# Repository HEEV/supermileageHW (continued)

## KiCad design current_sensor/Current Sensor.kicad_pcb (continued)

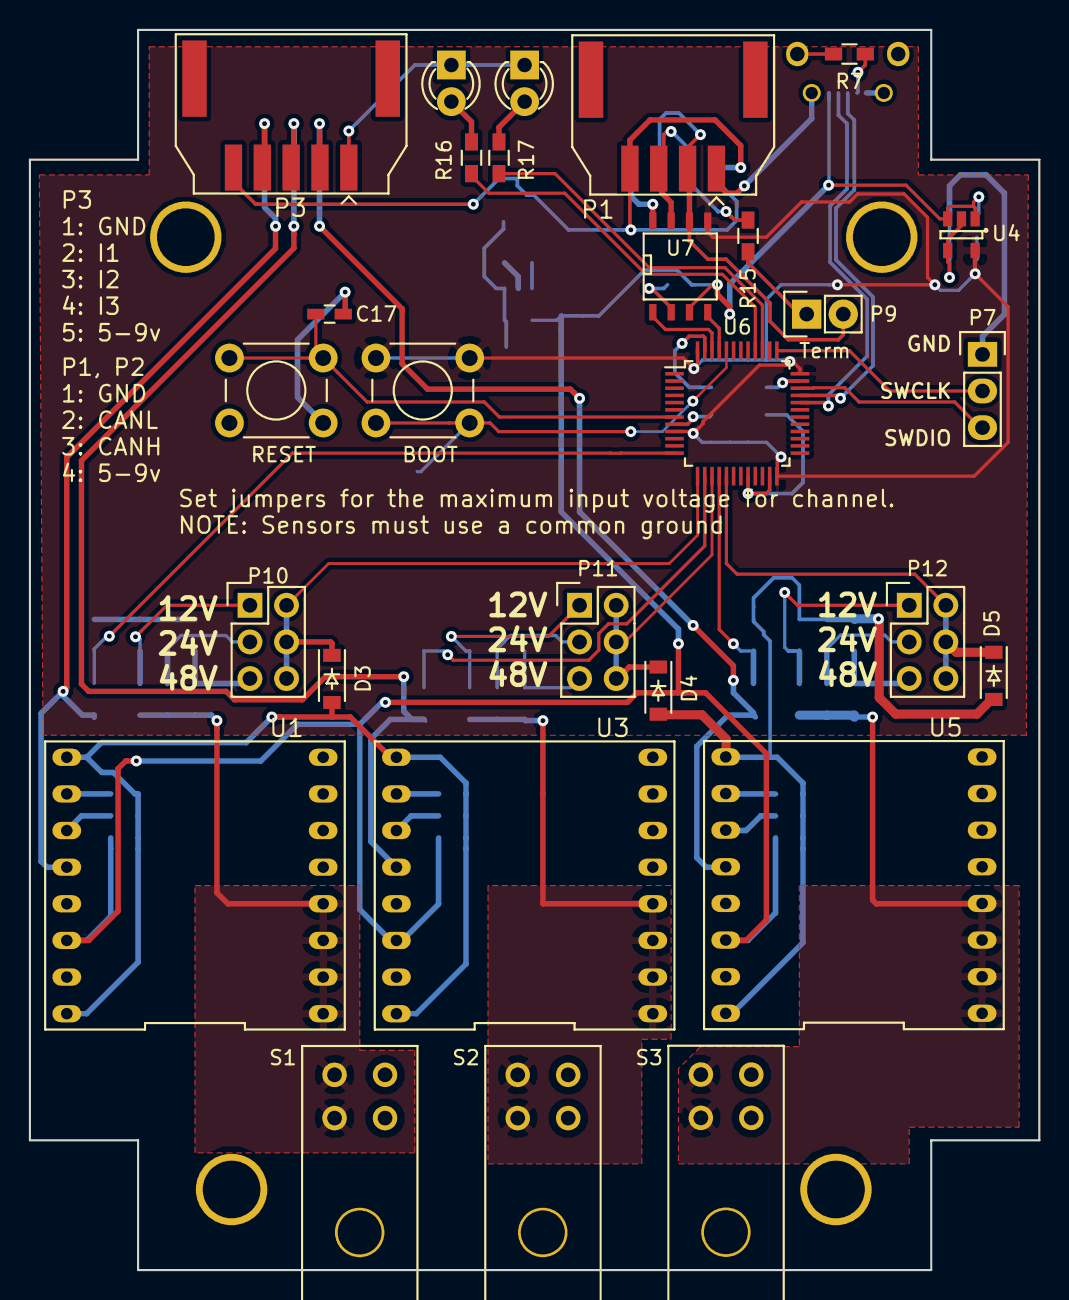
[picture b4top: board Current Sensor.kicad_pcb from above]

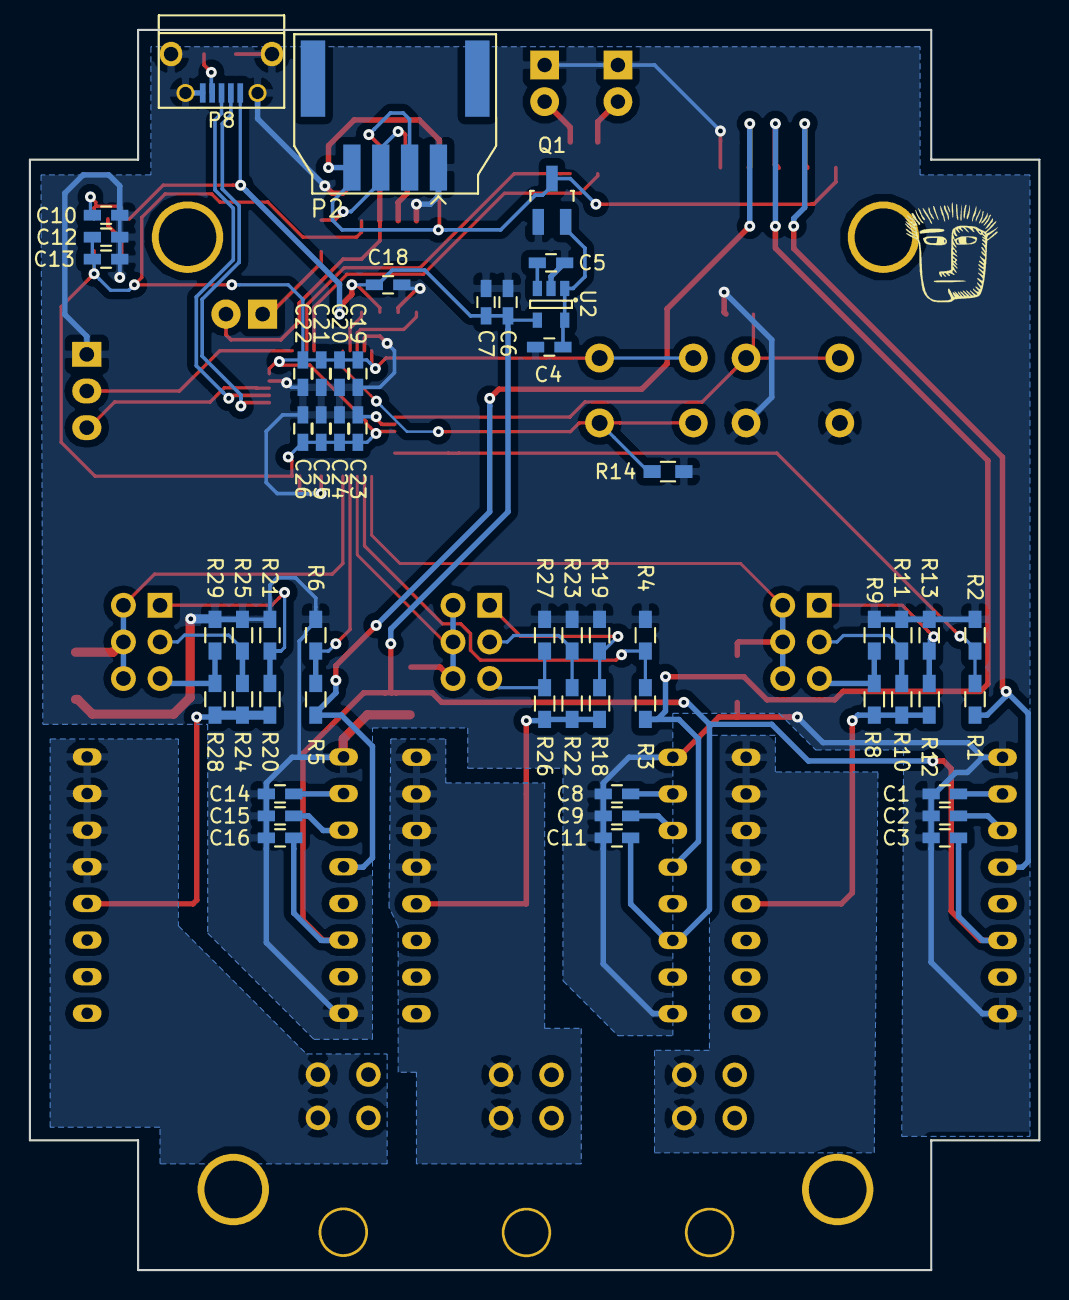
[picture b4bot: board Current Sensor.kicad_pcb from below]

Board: 2 copper layers, 70.0 x 86.0 mm, 82 parts (54 on the bottom side), 52 nets.

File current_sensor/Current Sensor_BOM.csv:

Reference,Value,Footprint,Count,Datasheet,FootprintLib,Distributor,PN
C1;C8;C14,1nf,C_0603_HandSoldering,3,,Capacitors_SMD,,
C23;C25;C21;C19,1uf,C_0603_HandSoldering,4,,Capacitors_SMD,Mouser,80-C0603C105K8P
C4;C5;C6;C3;C11;C16;C10;C13;C24;C18;C17;C26;C22;C20,0.1uf,C_0603_HandSoldering,14,,Capacitors_SMD,,
C7;C12,10uf,C_0603_HandSoldering,2,,Capacitors_SMD,,
C9;C15;C2,4.7nf,C_0603_HandSoldering,3,,Capacitors_SMD,,
D1,LED1,LED-3MM,1,,LEDs,,
D2,LED2,LED-3MM,1,,LEDs,,
D4;D3;D5;D7;D6;D8,D_Schottky_Small,SOD-123,6,,Diodes_SMD,Mouser,512-SS14FL 
P1,CAN_IN,Molex-duraClick-4conn,1,,User_Connectors,Mouser,538-502352-0400 
P10;P11;P12,CONN_02X03,Pin_Header_Straight_2x03,3,,Pin_Headers,,
P2,CAN_OUT,Molex-duraClick-4conn,1,,User_Connectors,Mouser,538-502352-0400 
P3,DuraClik-5,Molex-duraClick-5conn,1,,User_Connectors,Mouser,538-502352-0501 
P4;P5;P6,Ultra-Fit,Molex-UltraFit-2p,3,,Supermileage,Mouser,538-172310-2102 
P7,CONN_01X03,Pin_Header_Straight_1x03,1,,Pin_Headers,,
P8,USB,USB_Micro-B,1,,Connect,Mouser,649-10118194-0001LF
P9,CONN_01X02,Pin_Header_Straight_1x02,1,,Pin_Headers,,
Q1,Reverse,SOT-23_Handsoldering,1,,TO_SOT_Packages_SMD,Mouser,863-NTR3A30PZT1G 
R1;R3;R5,1k,R_0603_HandSoldering,3,,Resistors_SMD,,
R10;R22;R24,8k2,R_0603_HandSoldering,3,,Resistors_SMD,,
R12;R18;R20,4k7,R_0603_HandSoldering,3,,Resistors_SMD,,
R14;R7,100K,R_0603_HandSoldering,2,,Resistors_SMD,Mouser,71-CRCW0603-100K-E3
R15;R16;R17,120R,R_0603_HandSoldering,3,,Resistors_SMD,Mouser,71-CRCW0603-120-E3
R2;R4;R6,2k,R_0603_HandSoldering,3,,Resistors_SMD,,
R8;R26;R28,18k,R_0603_HandSoldering,3,,Resistors_SMD,Mouser,
R9;R11;R13;R27;R23;R19;R29;R25;R21,1k3,R_0603_HandSoldering,9,,Resistors_SMD,,
SW1,RESET,SW_PUSH_6mm,1,,Buttons_Switches_ThroughHole,,
SW2,BOOT,SW_PUSH_6mm,1,,Buttons_Switches_ThroughHole,,
U1;U3;U5,ACS710,DIP-16-SchmartBoard,3,,Supermileage,,
U2,NJM2870F0,SOT-23-5,1,,TO_SOT_Packages_SMD,Mouser,513-NJM2870F05-TE2 
U4,MIC5317,SOT-23-5,1,,TO_SOT_Packages_SMD,Mouser,998-MIC5317-3.3YM5TR 
U6,STM32F042C6,TQFP-48_7x7mm_Pitch0.5mm,1,,Housings_QFP,Mouser,511-STM32F042C6T6 
U7,mcp2562,SOIC-8-N,1,,SMD_Packages,Mouser,579-MCP2562-E/SN

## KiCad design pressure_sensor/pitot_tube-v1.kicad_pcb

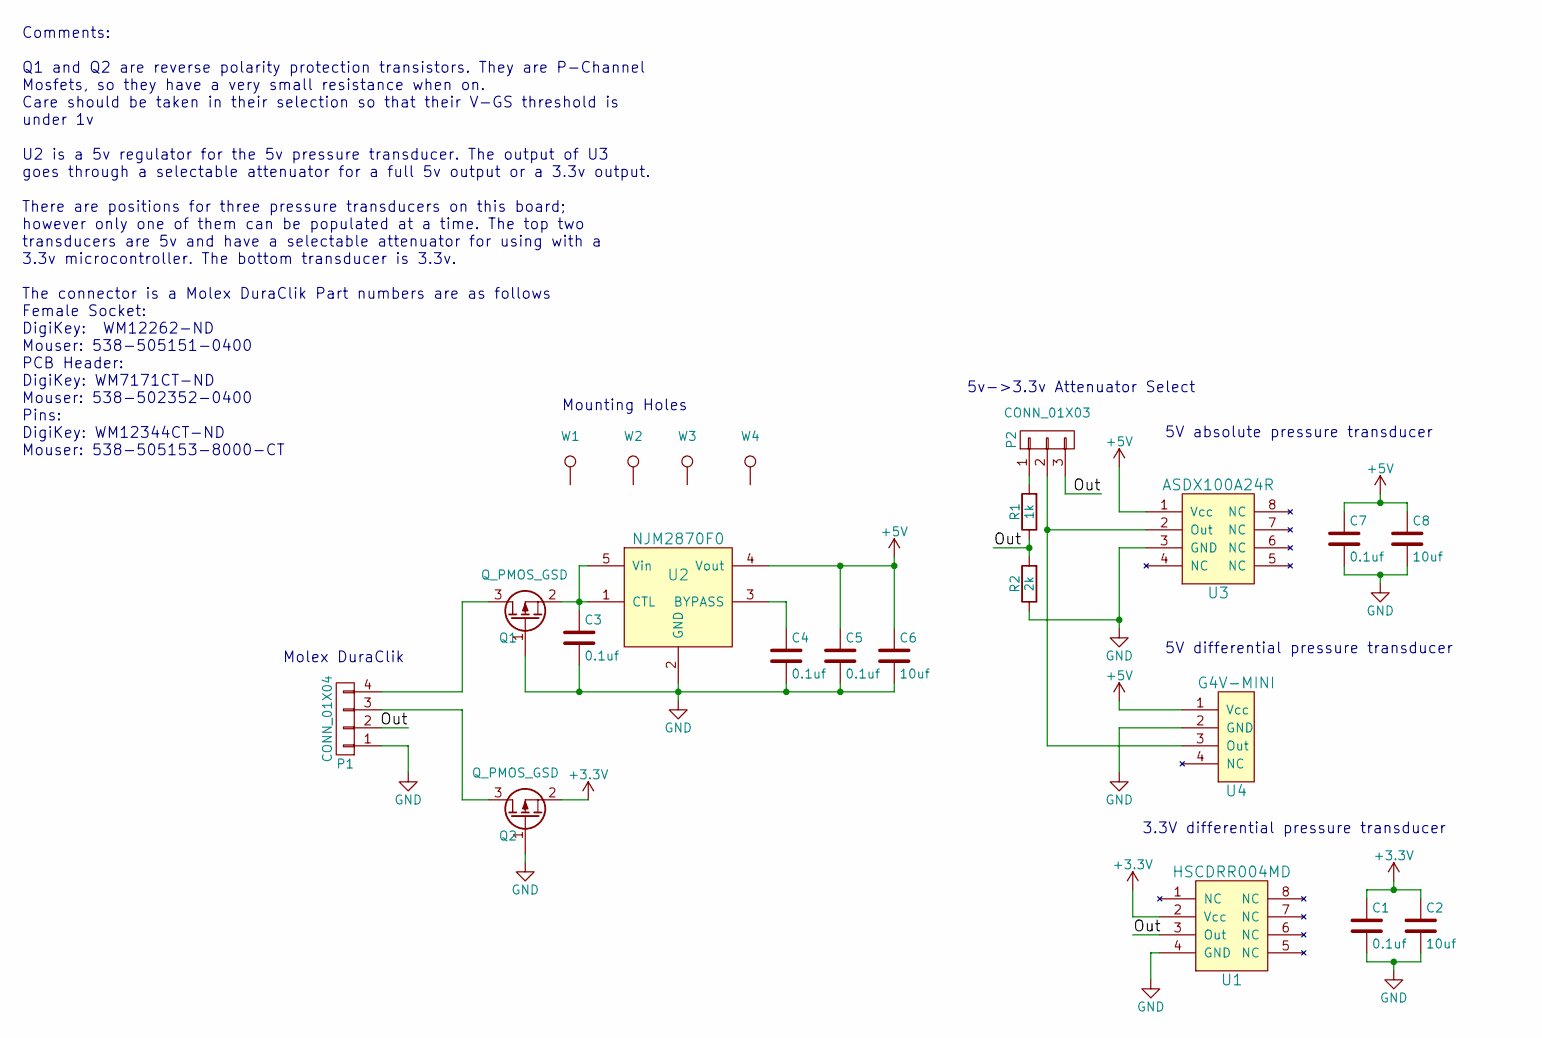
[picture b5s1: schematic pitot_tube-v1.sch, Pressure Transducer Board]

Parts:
C1, C3, C4, C5, C7: 0.1uf; C_0603_HandSoldering
C2, C6, C8: 10uf; C_0603_HandSoldering
P1: CONN_01X04; Molex-duraClick-4conn
P2: CONN_01X03; Pin_Header_Straight_1x03
Q1, Q2: Q_PMOS_GSD; SOT-23_Handsoldering
R1: 1k; R_0603_HandSoldering
R2: 2k; R_0603_HandSoldering
U1: HSCDRR004MD; DIP-8
U2: NJM2870F0; SOT-23-5
U3: ASDX100A24R
U4: G4V-MINI; Socket_Strip_Straight_1x04
W1, W2, W3, W4: Mount; MountingHole_2.2mm_M2

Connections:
+3V3: C1.1, C2.1, Q2.2 (S), U1.2 (Vcc)
+5V: C5.1, C6.1, C7.1, C8.1, U2.4 (Vout), U3.1 (Vcc), U4.1 (Vcc)
/Out: P1.2, P2.3, R1.1, R2.2, U1.3 (Out)
GND: C1.2, C2.2, C3.2, C4.2, C5.2, C6.2, C7.2, C8.2, P1.1, Q1.1 (G), Q2.1 (G), R2.1, U1.4 (GND), U2.2 (GND), U3.3 (GND), U4.2 (GND)
unnamed: C3.1, Q1.2 (S), U2.1 (CTL), U2.5 (Vin)
unnamed: C4.1, U2.3 (BYPASS)
unnamed: P1.3, Q2.3 (D)
unnamed: P1.4, Q1.3 (D)
unnamed: P2.1, R1.2
unnamed: P2.2, U3.2 (Out), U4.3 (Out)

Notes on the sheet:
Mounting Holes
Comments: Q1 and Q2 are reverse polarity protection transistors. They are P-Channel Mosfets, so they have a very small resistance when on. Care should be taken in their selection so that their V-GS threshold is under 1v U2 is a 5v regulator for the 5v pressure transducer. The output of U3 goes thro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
Molex DuraClik
5v->3.3v Attenuator Select
3.3V differential pressure transducer
5V absolute pressure transducer
5V differential pressure transducer

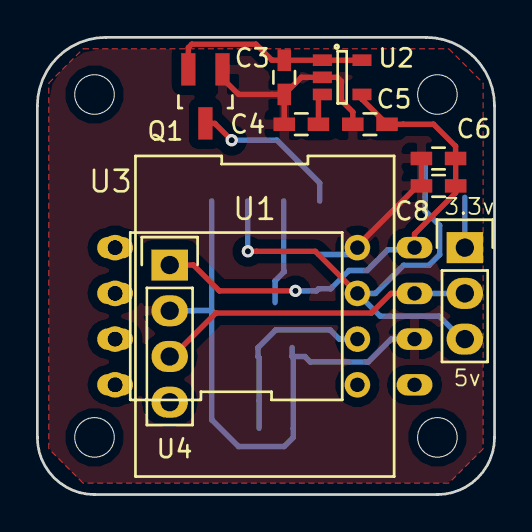
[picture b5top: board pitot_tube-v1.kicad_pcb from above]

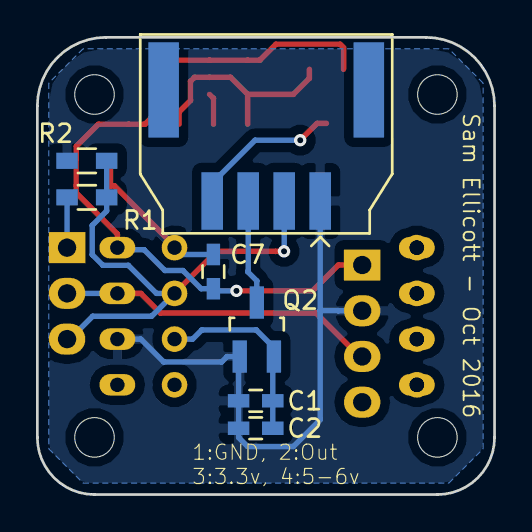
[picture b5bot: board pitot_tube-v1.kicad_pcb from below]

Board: 2 copper layers, 25.4 x 25.4 mm, 22 parts (7 on the bottom side), 10 nets.

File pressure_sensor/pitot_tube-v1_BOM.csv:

Reference,Value,Footprint,Count,Datasheet,FootprintLib,Distributor
U1,HSCDRR004MD,DIP-8,1,,supermileage,
P1,CONN_01X04,Molex-duraClick-4conn,1,,User_Connectors,
C1;C3;C4;C5;C7,0.1uf,C_0603_HandSoldering,5,,Capacitors_SMD,Mouser
C2;C6;C8,10uf,C_0603_HandSoldering,3,,Capacitors_SMD,
W1;W2;W3;W4,Mount,MountingHole_2.2mm_M2,4,,Mounting_Holes,
U2,NJM2870F0,SOT-23-5,1,,TO_SOT_Packages_SMD,
P2,CONN_01X03,Pin_Header_Straight_1x03,1,,Pin_Headers,
R1,1k,R_0603_HandSoldering,1,,Resistors_SMD,
R2,2k,R_0603_HandSoldering,1,,Resistors_SMD,
Q1;Q2,Q_PMOS_GSD,SOT-23_Handsoldering,2,,TO_SOT_Packages_SMD,
U3,ASDX100A24R,ASDX100A24R,1,,supermileage,
U4,G4V-MINI,Socket_Strip_Straight_1x04,1,,Socket_Strips,

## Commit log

2016-11-26 Added files for can_sensor and current_sensor.
2016-11-26 Added pressure sensor folder.
2016-11-26 added folder descriptions to the README
2016-11-26 fixing formating
2016-11-26 README.md edited online with Bitbucket
2016-11-26 moved the currrent sensor to a larger PCB
2016-11-27 Added all components to the board and finilized placement
2016-11-27 Finished PCB layout
2016-11-28 added more silkscreen text
2017-01-01 Added Sting schematic files to the repository.
    Fixed random labeling mistakes, added the CM0711 computer, and cleaned
    up the EFI_Breakout page.
2017-01-02 Added wiring diagrams to the repo.
    There are many changes from the original verion imported, mostly
    related to the computer. The computer was changed from the large CM3626
    to the CM0711. Many other smaller changes were made to increase
    readability.
2017-01-02 Filled in the Back_Of_Car page more.
2017-01-02 Upated Sting schematics to the most recent changes.
2017-01-04 Added new and improved relays to the parts library.
2017-01-04 Lots of small changes, major change to the relay box layout.
    Now using busses for the relay box.
2017-01-04 added gitignore file.
2017-01-04 Finished cleaning up the relay box wiring diagram.
2017-01-05 Ah, its finished (I think).
    Added the current sensor board into the wiring diagram, added titles to
    all pages, tried to make everything look pretty.
2017-01-05 Changed all page sizes to US Letter size, formatting errors.
2017-01-05 Added arduino page, small cleanup elsewhere.
2017-01-05 Added a 5v dc-dc converter part.
2017-01-05 Added 12v regulator, minor formatting mistakes.
2017-01-05 Added 12v regulator part.
2017-01-05 Added fuse before other components.
2017-01-05 "Nothing to see here!"
2017-01-05 Only really tiny formatting stuff.
2017-01-06 I'm not really sure what changed
2017-01-06 added Urbie turn signal light switch
2017-01-06 Added Urbie schematics to repo
2017-01-06 made the directory layout more sane
2017-01-06 Organizing relay box sheet
2017-01-06 Modified SPST switch to have an open and closed position
2017-01-07 cleaning up schematics
2017-01-07 Added files that changed names
2017-01-10 Added information to README.md
    Information about new folders.
2017-01-10 Formating error in README.md
2017-01-10 Fixed pdf output directories
2017-01-18 fixed some stuff
2017-01-18 nothing mutch
2017-01-18 Added EFI breakout folder
2017-01-18 added 4p duraclik connector
2017-01-28 added Urbie wiring diagrams
2017-02-01 Added stuff
2017-02-01 added library pathes file
2017-03-07 Updated for pcb creation
2017-03-07 made efi breakout pcb
2017-03-07 Fixed boot button going to boot1 instead of boot0
2017-03-07 Fixed boot button going to boot1 instead of boot0.
    Current sensor board
2017-03-07 Moved to four pin Molex UltraFit connectors.
    Required rearanging layout slightly.
2017-03-07 Made names consistant across pages
2017-03-07 added Starter_Relay part
2017-03-07 fixed missing parts updated sensor boards
2017-03-07 updated file
2017-03-17 Added pdf of can_sensor schematic.
2017-03-18 updated 1593BB-box footprint
2017-03-18 updated wiring diagrams
2017-03-18 updated hole location on 1593BB box
2017-05-25 I don't know what changed
2017-06-18 revised CanSensor board to v2.0
    * Jumper to enable and disable 120 Ohm termination resistor
    * IO pin to mcp2562 to enable disable the CAN tranciever
    * Replaced input protection diodes with a zener diode
    * Replaced reverse battery protection diode with a transistor (ideal diode)
    * Better silkscreen comments
2017-06-18 added 3d models
2017-07-08 updated Current Sensor board with changes made to CanSensor (zener diodes)
2017-09-20 added DPDT switch for Hazard lights on Urbie
2017-09-23 Wire coloring
    Worked on labeling the color of the wires
2017-09-30 Changed computer sheet in Urbie Wiring diagrams
2017-10-01 added a relay to enable the starter relay
2017-10-02 Moved where the relay to turn on the starter relay gets power from
2017-12-06 Started project folder Kark
    This contains the master power distrobution pcb outline
2018-01-13 Karch power prepped for PCB
    Added reisitor values
    Assigned footprints
    small organizational changes
2018-01-20 Started PCB art
    Added mounting pin templates.
    started the PCB first draft.
2018-01-20 EFI Breakout
    Changed Ignition and Injection GND wires to power
2018-01-20 EFI Breakout
    Added extra "bread board test pins"
2018-01-20 PCB Developed Further
    Organized and optimized part layout.
    (wires not started)
2018-01-27 Kark Power PCB tracks developed
    The PCB tracks were developed and laid with default thicknesses for the main systems.
2018-01-27 Karch PCB
    Critical Wires Thickened some Silk Screen added.
2018-02-01 Routed EFI
2018-02-03 Finishing touches on Kark Power
    Added Silk screen
    Fixed some bugs
2018-02-03 Plotted PCB,Drill File
    Created the files in question
2018-02-10 Fitted board to box
    Slightly changed dimentions, tracings and text to fit the selected electrical box
2018-02-10 Kark Power
    Made ground planes fit board.
2018-02-10 Visual formatting
    Moved silk screen to avoid confliction
    caused part numbers on the protoype area to not appear in silkscreen
    Updated the footprints to with pin designators in the silkscreen.
2018-02-10 Final Formatting for production
    Edited text and added labeles.
    Added power and ground on the test area.
    Updated authors and year.
2018-02-10 Save because ?
2018-02-23 messed with silkscreen, generated gerbers
2018-03-17 modified EFI_Breakout
2018-03-17 Kark Schematics
2018-03-17 Integrated Power Board layout
    Added the schematic version of the content of the Power Board PCB.
    Added an extra battery for the Engine.
    Changed enables from copy of Sting system to regulation.
2018-03-17 Minor changes to first page.
2018-03-24 Added Canopy Switches to Sting Documentation
2018-03-24 Messed with Kark
2018-03-24 Added Starter and Fuel pump
2018-03-24 CM711 Computer
2018-03-24 Schematic corrections
    Corrected wiring for fuel pump and moved the EFI chip over to accomodate the change
2018-03-24 Second Page
2018-03-24 Kark Schematic additions
    Fixed fuel pump
    Added wheel sheetand digital switches
2018-03-24 wheelsheet
    Added MC pin inputs
2018-03-24 Created can breakout
    Added can boards fro sensors and integrated the computer to the can system.
    Created the Can powering system.
2018-03-24 Added Can stuff
2018-03-24 Modified CanNode for steerining wheel
2018-03-24 minor edits
2018-03-25 Finished Schematics
2018-03-25 removed files
2018-03-25 Added EFI Breakout File
2018-03-25 Changed Paper size, version number
2019-03-23 Adding Madeline's files
2019-03-23 Added rescue files
2019-03-24 added things, namely edited EFI_BREAKOUT
2019-05-18 Removed EFI system and CAN based control from the Karch schematics
2019-05-18 Added Karch schematics
2019-09-10 changes made last year
